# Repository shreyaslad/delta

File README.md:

# Delta

Delta is a minature, custom board that remotely control vehicles, connecting to the Onboard Diagnostics (OBD-II) port and streaming real-time onboard sensor data such as:

- Speed
- Acceleration
- Gyroscopic Tilt
- Throttle & Steering Position
- Gear
- Engine RPM

and integrating external cameras and sensors.

Delta supports WiFi and Bluetooth LE, running a dual-core ESP32-S3R8V based on the 32-bit Xtensa architecture. The current prototype is only 32mm * 37mm with single-sided assembly, packing a ton of components into an incredibly small area. Delta can be powered by a computer through the USB Type-C port or independantly with a 12v car battery.

## Project Structure

```
.
├── docs        : Project documentation
├── firmware    : Delta firmware
├── iot         : AWS IoT infrastructure
├── pcb         : KiCad PCB design files
└── README.md
```

## Hardware

Features:
- USB Type-C connector
- 12v -> 5v @ 3A Buck Converter
- 5v -> 3.3v @ 700mA Low Dropout Regulator
- Dual Core ESP32-S3R8V microcontroller
    - Ultra-low current deep sleep
- 2.4GHz 802.11/b/g/n WiFi
- Bluetooth Low Energy
- CAN bus communication
- Neopixel support

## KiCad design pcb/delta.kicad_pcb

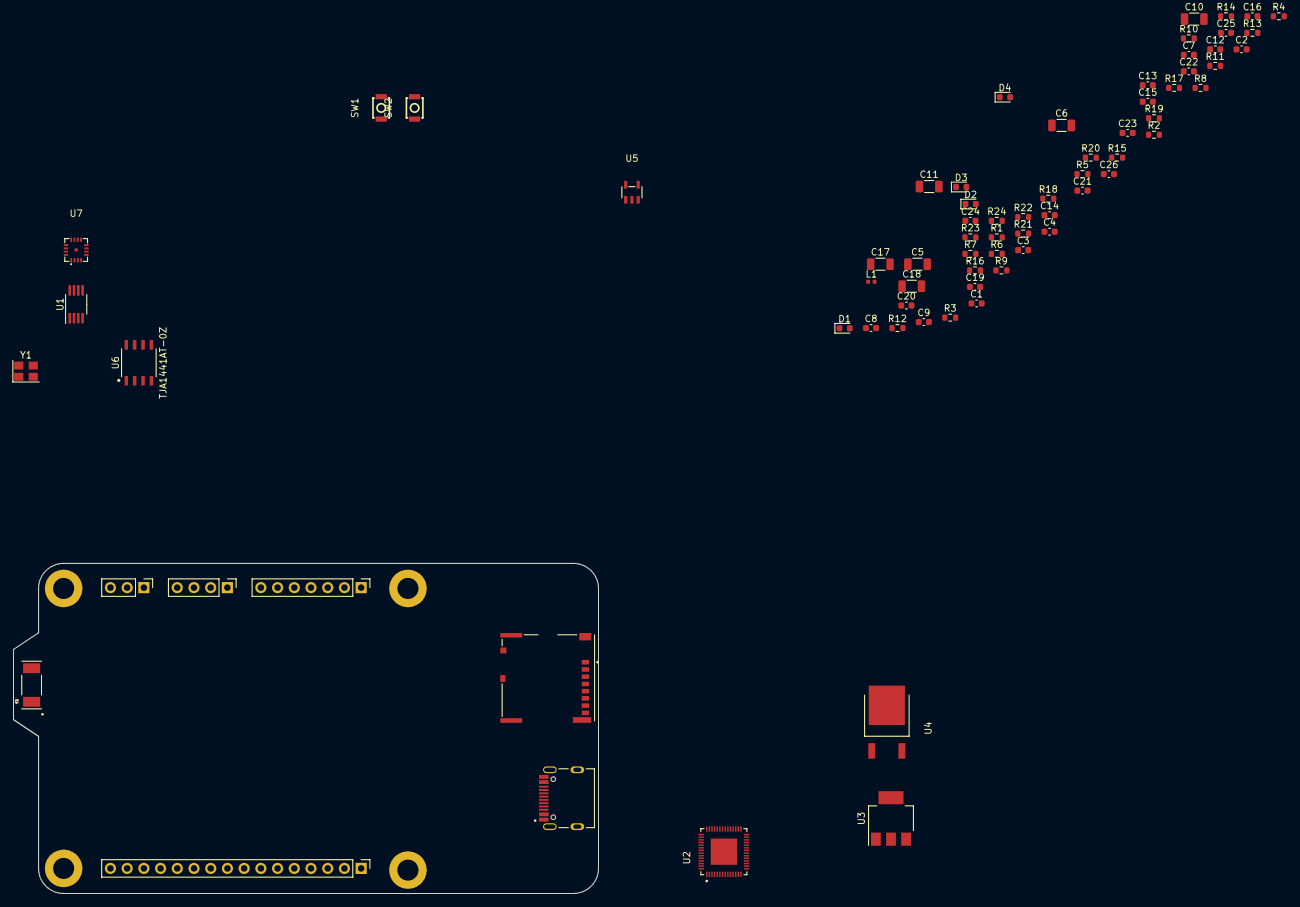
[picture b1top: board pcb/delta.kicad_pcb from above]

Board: 4 copper layers, 88.9 x 50.2 mm, 76 parts (0 on the bottom side), 51 nets, no tracks yet.

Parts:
C1, C3, C4, C13, C14, C15, C16, C19, C22: 1uF; C_0603_1608Metric
C2: 2pF; C_0603_1608Metric
C5, C6, C10, C11, C17, C18: 1uF; C_1206_3216Metric
C7: 10uF; C_0603_1608Metric
C8, C9: 12pF; C_0603_1608Metric
C12, C20, C21, C24, C25, C26: 0.1uF; C_0603_1608Metric
C23: 4.7nF; C_0603_1608Metric
D1: PWR BLUE; LED_0603_1608Metric
D2, D4: D; D_0603_1608Metric
D3: GREEN; LED_0603_1608Metric
E1: NN01-102; XCVR_NN01-102
H1, H2, H3, H4: MountingHole_Pad; MountingHole_3.2mm_M3_ISO7380_Pad
J1: USB_C_Receptacle_USB2.0; HRO_TYPE-C-31-M-12
J2: Conn_01x03; PinHeader_1x03_P2.54mm_Vertical
J3: Conn_01x04; PinHeader_1x04_P2.54mm_Vertical
J4: Conn_01x07; PinHeader_1x07_P2.54mm_Vertical
J5: Conn_01x16; PinHeader_1x16_P2.54mm_Vertical
J6: Micro_SD_Card; MOLEX_503398-1892
L1: 5.1nH; L_0402_1005Metric
R1, R3, R9, R10, R11, R15, R16, R17, R18, R19, R20, R21, R22, R23, R24: 10k; R_0603_1608Metric
R2, R4: 27; R_0603_1608Metric
R5: 270; R_0603_1608Metric
R6, R7: 5.1k; R_0603_1608Metric
R8, R12: 1k; R_0603_1608Metric
R13, R14: 60; R_0603_1608Metric
SW1: RESET; SW-SMD_L3.0-W2.5-P3.40-LS4.0-L
SW2: FLASH; SW-SMD_L3.0-W2.5-P3.40-LS4.0-L
U1: PI4ULS5V202UEX; MSOP-8_3x3mm_P0.65mm
U2: ESP32-S3R8V; QFN40P700X700X90-57N
U3: C401677; SOT-223
U4: CJ78053%; TO-252-2_L6.6-W6.1-P4.58-LS10.1-BR-CW
U5: TPRT9193-18GB; SOT-23-5_L3.0-W1.7-P0.95-LS2.8-BL
U6: TJA1441AT-0Z; TJA1441DT-0Z
U7: QST_QMI8610; LGA-16_L3.3-W3.3-P0.50-BL-EP0.5
Y1: 40 MHz; Crystal_SMD_3225-4Pin_3.2x2.5mm

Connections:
+1V8: C21.1, C25.1, U5.5 (VOUT), U7.8 (VDDd), U7.9 (SA0)
+3V3: C1.1, C7.1, C12.1, C13.1, C14.1, C15.1, C16.1, C17.1, C19.1, C20.1, C24.1, C26.1, J6.4 (VDD), R3.1, R10.1, R15.1, R17.1, R18.1, R19.1, R20.1, R21.1, R22.1, R23.1, R24.1, U1.1 (VCCA), U1.5 (EN), U2.2 (VDD3P3), U2.3 (VDD3P3), U2.20 (VDD3P3_RTC), U2.29 (VDD_SPI), U2.46 (VDD3P3_CPU), U2.55 (VDDA1), U2.56 (VDDA2), U3.3 (VOUT), U5.1 (VIN), U5.3 (EN), U7.2 (VDDa)
/ACCEL_CS: U2.6 (GPIO1), U7.10 (CS)
/ACCEL_INT1: U2.9 (GPIO4), U7.12 (INT1)
/ACCEL_INT2: U2.10 (GPIO5), U7.11 (INT2)
/ACCEL_RST: U2.7 (GPIO2), U7.16 (RST)
/ESP32_Rx: J3.1, U2.50 (U0RXD)
/ESP32_Tx: J3.2, U2.49 (U0TXD)
/ESP32_U0CTS: J3.3, U2.22 (XTAL_32K_N)
/ESP32_U0RTS: J3.4, U2.21 (XTAL_32K_P)
/ESP32_XTAL_N: C9.2, U2.53 (XTAL_N), Y1.1
/ESP32_XTAL_P: C8.2, U2.54 (XTAL_P), Y1.3
/NEOPXL_DIN: U1.2 (A1), U2.14 (GPIO9)
/NEOPXL_DIN_5v: J2.1, R5.2
/OBD_12v: C11.1, J5.7, U4.1 (VIN)
/OBD_CANH: J5.9, R13.1, U6.7 (CANH)
/OBD_CANL: J5.10, R14.2, U6.6 (CANL)
/OBD_Rx: U2.23 (GPIO17), U6.4 (RXD)
/OBD_Tx: U2.24 (GPIO18), U6.1 (TXD)
/SCL: R17.2, U2.11 (GPIO6), U7.14 (SCL)
/SDA: R18.2, U2.12 (GPIO7), U7.13 (SDA)
/SD_CLK: J6.5 (CLK), R21.2, U2.33 (SPICLK)
/SD_CMD: J6.3 (CMD), R22.2, U2.35 (SPID)
/SD_D0: J6.7 (DAT0), R20.2, U2.34 (SPIQ)
/SD_D1: J6.8 (DAT1), R19.2, U2.31 (SPIWP)
/SD_D2: J6.1 (DAT2), R24.2, U2.30 (SPIHD)
/SD_D3: J6.2 (DAT3/CD), R23.2, U2.32 (SPICS0)
/USB_D+: R2.2, U2.26 (GPIO20)
/USB_D-: R4.2, U2.25 (GPIO19)
GND: C1.2, C3.2, C4.2, C5.2, C6.2, C7.2, C8.1, C9.1, C10.2, C11.2, C12.2, C13.2, C14.2, C15.2, C16.2, C17.2, C18.2, C19.2, C20.2, C21.2, C22.2, C23.2, C24.2, C25.2, C26.2, H1.1, H2.1, H3.1, H4.1, J1.A1 (GND), J1.S1 (SHIELD), J2.3, J6.6 (VSS), J6.9 (SHIELD), L1.1, R6.2, R7.2, R8.2, R9.2, R11.2, R12.2, R16.2, SW1.2, SW2.2, U1.4 (GND), U2.57 (GND), U3.2 (GND), U4.2 (GND), U5.2 (GND), U6.2 (GND), U7.3 (GND), U7.15 (GND), Y1.2, Y1.4
unnamed: C2.1, E1.1, L1.2
unnamed: C2.2, U2.1 (LNA_IN)
unnamed: C3.1, R1.1, SW1.1
unnamed: C5.1, C6.1, D1.2 (A), D2.2 (A), J1.A4 (VBUS)
unnamed: C18.1, D4.2 (A), U4.3 (VOUT)
unnamed: C23.1, R13.2, R14.1
unnamed: D1.1 (K), R8.1
unnamed: D3.1 (K), R12.1
unnamed: D3.2 (A), U2.27 (GPIO21)
unnamed: J1.A5 (CC1), R7.1
unnamed: J1.A6 (D+), J1.B6 (D+), R2.1
unnamed: J1.A7 (D-), J1.B7 (D-), R4.1
unnamed: J1.B5 (CC2), R6.1
unnamed: R1.2, R3.2, U2.4 (CHIP_PU)
unnamed: R5.1, U1.7 (B1)
unnamed: R9.1, U2.52 (GPIO46)
unnamed: R10.2, SW2.1, U2.5 (GPIO0)
unnamed: R11.1, U2.8 (GPIO3)
unnamed: R15.2, U6.5 (S_N)
unnamed: R16.1, U6.8 (OFF)
VBUS: C4.1, C10.1, C22.1, D2.1 (K), D4.1 (K), J2.2, U1.8 (VCCB), U3.1 (VIN), U6.3 (VCC)

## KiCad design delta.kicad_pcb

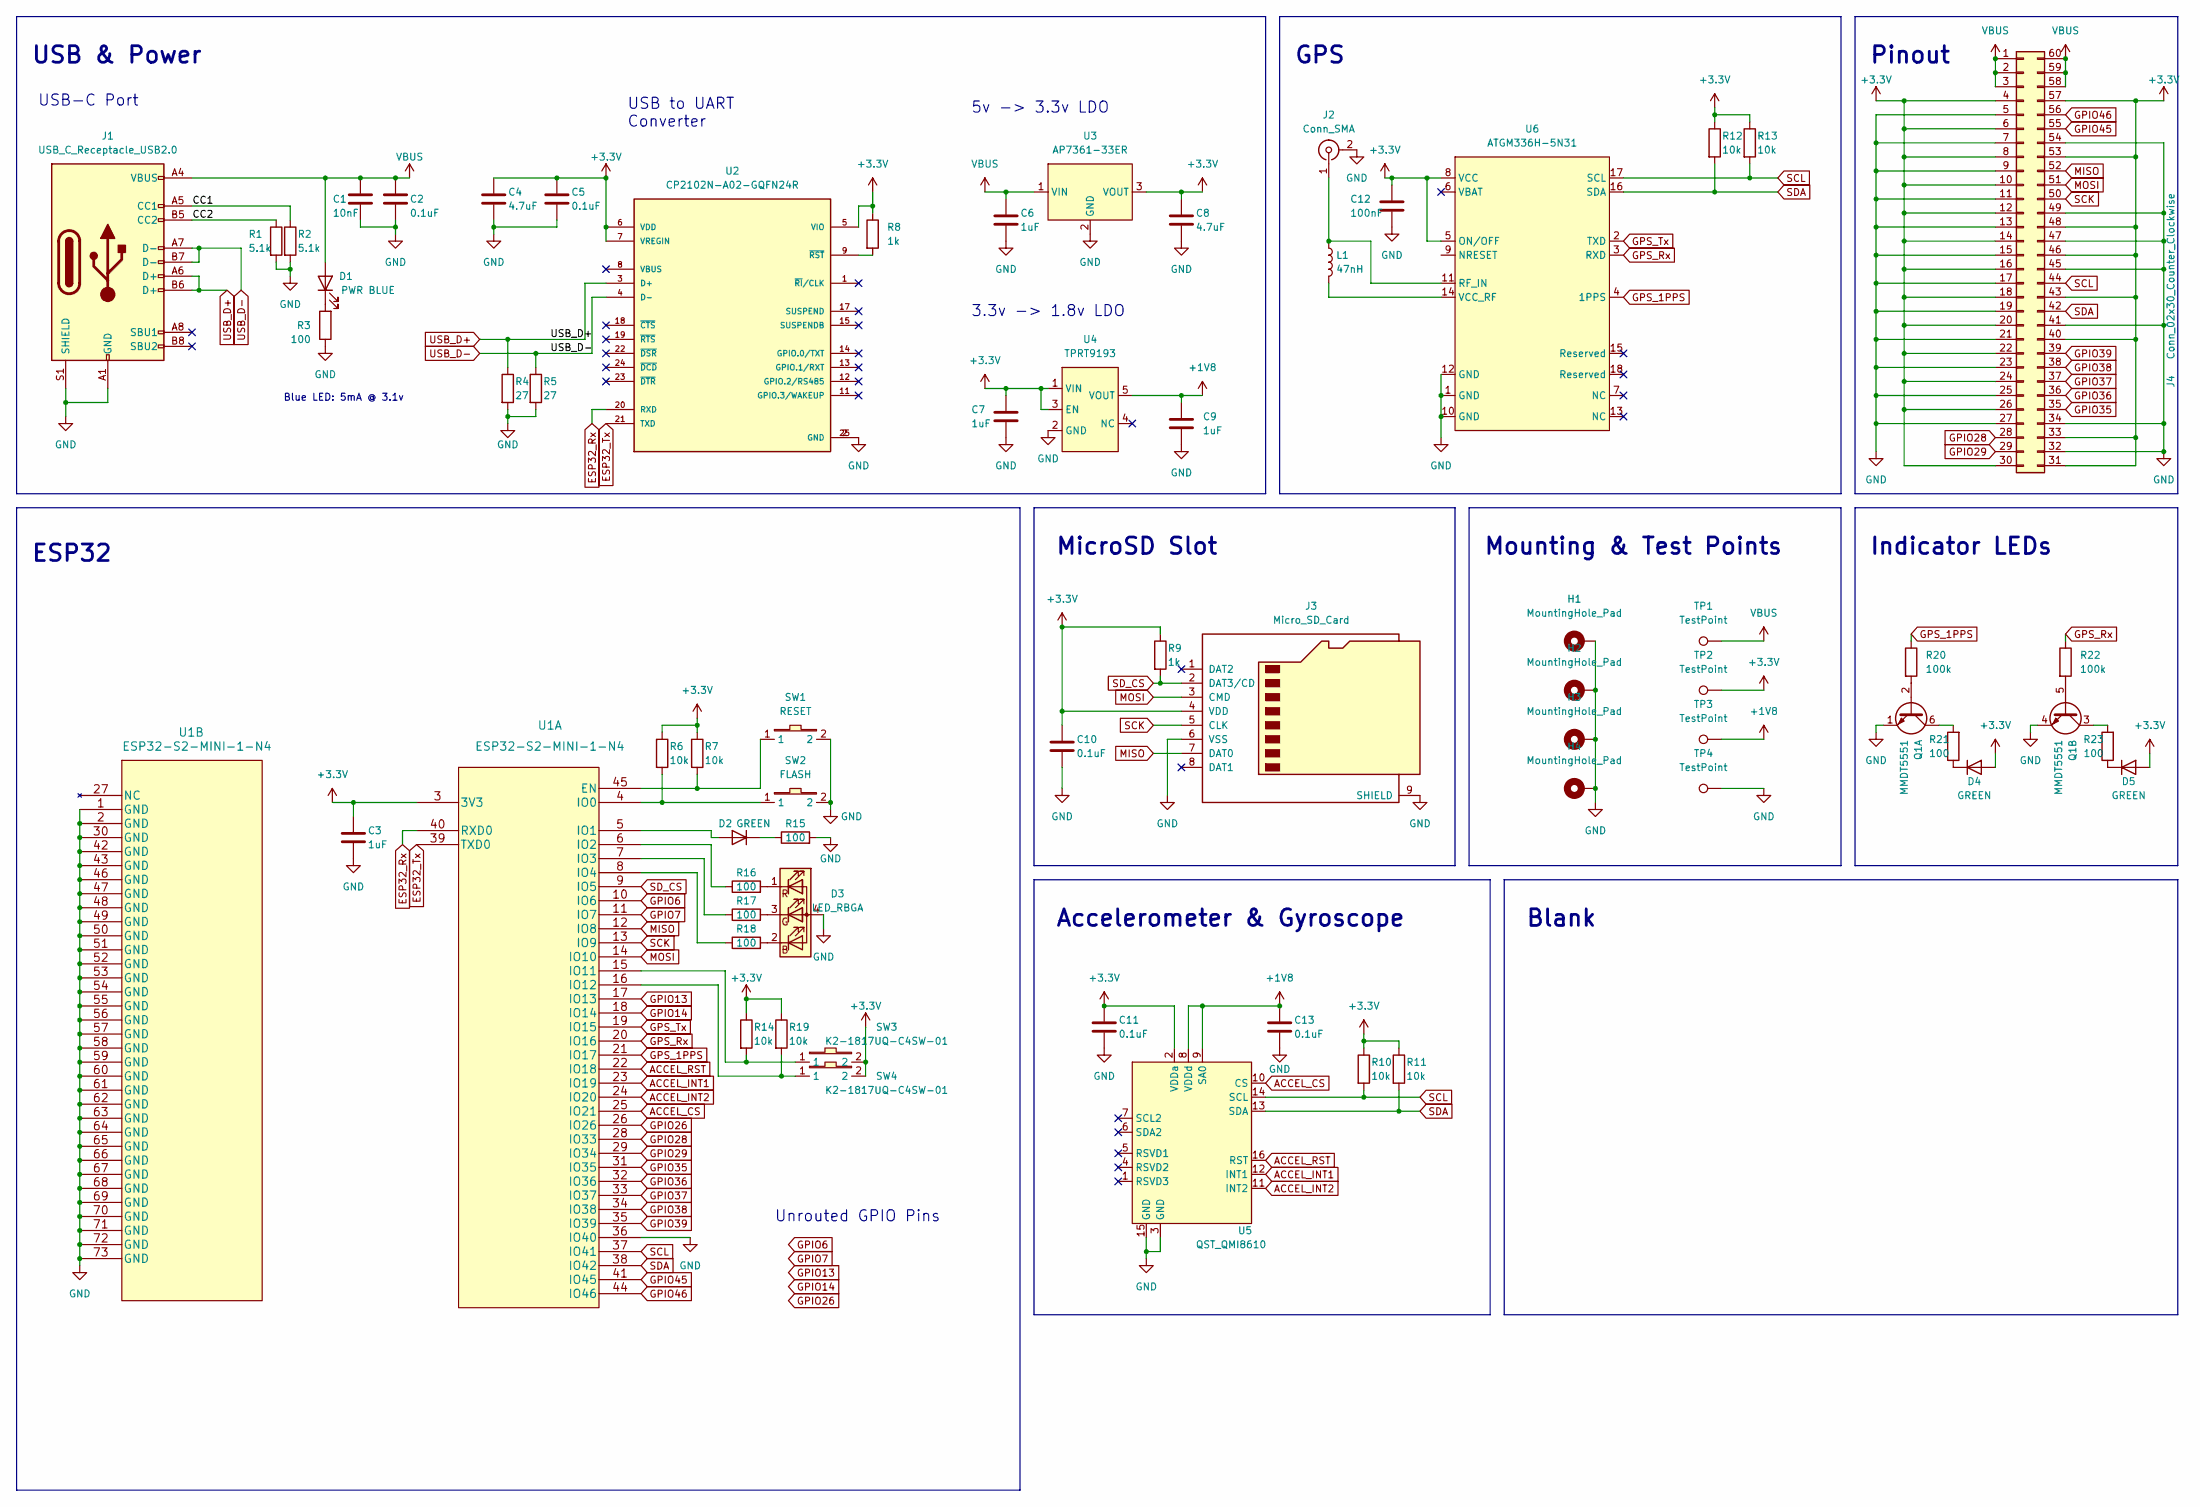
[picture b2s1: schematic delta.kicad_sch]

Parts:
C1: 10nF; C_1206_3216Metric
C2: 0.1uF; C_1206_3216Metric
C3, C6: 1uF; C_1206_3216Metric
C4: 4.7uF; C_0603_1608Metric
C5, C10, C11, C13: 0.1uF; C_0603_1608Metric
C7, C9: 1uF; C_0603_1608Metric
C8: 4.7uF; C_1206_3216Metric
C12: 100nF; C_0603_1608Metric
D1: PWR BLUE; LED_0805_2012Metric
D2: GREEN; LED_0805_2012Metric
D3: LED_RBGA; LED_RGB_1210
D4, D5: GREEN; LED_0603_1608Metric
H1, H2, H3, H4: MountingHole_Pad; MountingHole_3.2mm_M3_ISO7380_Pad
J1: USB_C_Receptacle_USB2.0; HRO_TYPE-C-31-M-12
J2: Conn_SMA; ANT-SMD_1909763-1
J3: Micro_SD_Card; MOLEX_503398-1892
J4: Conn_02x30_Counter_Clockwise; PinHeader_2x30_P2.00mm_Vertical
L1: 47nH; L_0603_1608Metric
Q1: MMDT5551; SOT-363_SC-70-6
R1, R2: 5.1k; R_0603_1608Metric
R3, R15, R16, R17, R18, R21, R23: 100; R_0603_1608Metric
R4, R5: 27; R_0603_1608Metric
R6, R7, R10, R11, R12, R13, R14, R19: 10k; R_0603_1608Metric
R8, R9: 1k; R_0603_1608Metric
R20, R22: 100k; R_0603_1608Metric
SW1: RESET; KEY-SMD_2P-L6.0-W6.0-P6.00; LCSC Part C128939
SW2: FLASH; KEY-SMD_2P-L6.0-W6.0-P6.00; LCSC Part C128939
SW3, SW4: K2-1817UQ-C4SW-01; KEY-SMD_2P-L6.0-W6.0-P6.00; LCSC Part C128939
TP1, TP2, TP3, TP4: TestPoint; TestPoint_Pad_D3.0mm
U1: ESP32-S2-MINI-1-N4
U2: CP2102N-A02-GQFN24R; QFN50P400X400X80-25N; PARTREV 1.3
U3: AP7361-33ER; SOT-223
U4: TPRT9193; SOT-23-5_L3.0-W1.7-P0.95-LS2.8-BL
U5: QST_QMI8610; LGA-16_L3.3-W3.3-P0.50-BL-EP0.5
U6: ATGM336H-5N31; GPSM-SMD_ATGM336H-TR; LCSC Part C90770

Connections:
+1V8: C9.1, C13.1, TP3.1, U4.5 (VOUT), U5.8 (VDDd), U5.9 (SA0)
+3V3: C3.1, C4.1, C5.1, C7.1, C8.1, C10.1, C11.1, C12.1, D4.2 (A), D5.2 (A), J3.4 (VDD), J4.4, J4.6, J4.8, J4.10, J4.12, J4.14, J4.16, J4.18, J4.20, J4.22, J4.24, J4.26, J4.30, J4.31, J4.33, J4.40, J4.43, J4.46, J4.48, J4.53, J4.57, R6.1, R7.1, R8.1, R9.1, R10.1, R11.1, R12.1, R13.1, R14.1, R19.1, SW3.2, SW4.2, TP2.1, U1.3 (3V3), U2.5 (VIO), U2.6 (VDD), U2.7 (VREGIN), U3.3 (VOUT), U4.1 (VIN), U4.3 (EN), U5.2 (VDDa), U6.5 (ON/OFF), U6.8 (VCC)
/CC1: J1.A5 (CC1), R2.1
/CC2: J1.B5 (CC2), R1.1
ACCEL_CS: U1.25 (IO21), U5.10 (CS)
ACCEL_INT1: U1.23 (IO19), U5.12 (INT1)
ACCEL_INT2: U1.24 (IO20), U5.11 (INT2)
ACCEL_RST: U1.22 (IO18), U5.16 (RST)
ESP32_Rx: U1.40 (RXD0), U2.20 (RXD)
ESP32_Tx: U1.39 (TXD0), U2.21 (TXD)
GND: C1.2, C2.2, C3.2, C4.2, C5.2, C6.2, C7.2, C8.2, C9.2, C10.2, C11.2, C12.2, C13.2, D3.4 (A), H1.1, H2.1, H3.1, H4.1, J1.A1 (GND), J1.A12 (GND), J1.B1 (GND), J1.B12 (GND), J1.S1 (SHIELD), J2.2 (Ext), J3.6 (VSS), J3.9 (SHIELD), J4.5, J4.7, J4.9, J4.11, J4.13, J4.15, J4.17, J4.19, J4.21, J4.23, J4.25, J4.27, J4.32, J4.34, J4.41, J4.45, J4.47, J4.49, J4.54, Q1.1 (E1), Q1.4 (E2), R1.2, R2.2, R3.1, R4.2, R5.2, R15.2, SW1.2, SW2.2, TP4.1, U1.1 (GND), U1.2 (GND), U1.30 (GND), U1.36 (IO40), U1.42 (GND), U1.43 (GND), U1.46 (GND), U1.47 (GND), U1.48 (GND), U1.49 (GND), U1.50 (GND), U1.51 (GND), U1.52 (GND), U1.53 (GND), U1.54 (GND), U1.55 (GND), U1.56 (GND), U1.57 (GND), U1.58 (GND), U1.59 (GND), U1.60 (GND), U1.61 (GND), U1.62 (GND), U1.63 (GND), U1.64 (GND), U1.65 (GND), U1.66 (GND), U1.67 (GND), U1.68 (GND), U1.69 (GND), U1.70 (GND), U1.71 (GND), U1.72 (GND), U1.73 (GND), U2.2 (GND), U2.25 (GND), U3.2 (GND), U4.2 (GND), U5.3 (GND), U5.15 (GND), U6.1 (GND), U6.10 (GND), U6.12 (GND)
GPIO6: U1.10 (IO6)
GPIO7: U1.11 (IO7)
GPIO13: U1.17 (IO13)
GPIO14: U1.18 (IO14)
GPIO26: U1.26 (IO26)
GPIO28: J4.28, U1.28 (IO33)
GPIO29: J4.29, U1.29 (IO34)
GPIO35: J4.35, U1.31 (IO35)
GPIO36: J4.36, U1.32 (IO36)
GPIO37: J4.37, U1.33 (IO37)
GPIO38: J4.38, U1.34 (IO38)
GPIO39: J4.39, U1.35 (IO39)
GPIO45: J4.55, U1.41 (IO45)
GPIO46: J4.56, U1.44 (IO46)
GPS_1PPS: R20.1, U1.21 (IO17), U6.4 (1PPS)
GPS_Rx: R22.1, U1.20 (IO16), U6.3 (RXD)
GPS_Tx: U1.19 (IO15), U6.2 (TXD)
MISO: J3.7 (DAT0), J4.52, U1.12 (IO8)
MOSI: J3.3 (CMD), J4.51, U1.14 (IO10)
unnamed: D1.1 (K), R3.2
unnamed: D2.1 (K), R15.1
unnamed: D2.2 (A), U1.5 (IO1)
unnamed: D3.1 (RK), R16.2
unnamed: D3.2 (BK), R18.2
unnamed: D3.3 (GK), R17.2
unnamed: D4.1 (K), R21.1
unnamed: D5.1 (K), R23.1
unnamed: J2.1 (In), L1.1, U6.11 (RF_IN)
unnamed: L1.2, U6.14 (VCC_RF)
unnamed: Q1.2 (B1), R20.2
unnamed: Q1.3 (C2), R23.2
unnamed: Q1.5 (B2), R22.2
unnamed: Q1.6 (C1), R21.2
unnamed: R6.2, SW2.1, U1.4 (IO0)
unnamed: R7.2, SW1.1, U1.45 (EN)
unnamed: R8.2, U2.9 (~RST)
unnamed: R14.2, SW3.1, U1.15 (IO11)
unnamed: R16.1, U1.6 (IO2)
unnamed: R17.1, U1.7 (IO3)
unnamed: R18.1, U1.8 (IO4)
unnamed: R19.2, SW4.1, U1.16 (IO12)
SCK: J3.5 (CLK), J4.50, U1.13 (IO9)
SCL: J4.44, R10.2, R13.2, U1.37 (IO41), U5.14 (SCL), U6.17 (SCL)
SDA: J4.42, R11.2, R12.2, U1.38 (IO42), U5.13 (SDA), U6.16 (SDA)
SD_CS: J3.2 (DAT3/CD), R9.2, U1.9 (IO5)
USB_D+: J1.A6 (D+), J1.B6 (D+), R4.1, U2.3 (D+)
USB_D-: J1.A7 (D-), J1.B7 (D-), R5.1, U2.4 (D-)
VBUS: C1.1, C2.1, C6.1, D1.2 (A), J1.A4 (VBUS), J1.A9 (VBUS), J1.B4 (VBUS), J1.B9 (VBUS), J4.1, J4.2, J4.3, J4.58, J4.59, J4.60, TP1.1, U3.1 (VIN)

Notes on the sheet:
MicroSD Slot
Accelerometer & Gyroscope
Blue LED: 5mA @ 3.1v
Pinout
USB to UART Converter
Mounting & Test Points
USB-C Port
3.3v -> 1.8v LDO
5v -> 3.3v LDO
Unrouted GPIO Pins
GPS
Indicator LEDs
Blank
ESP32
USB & Power

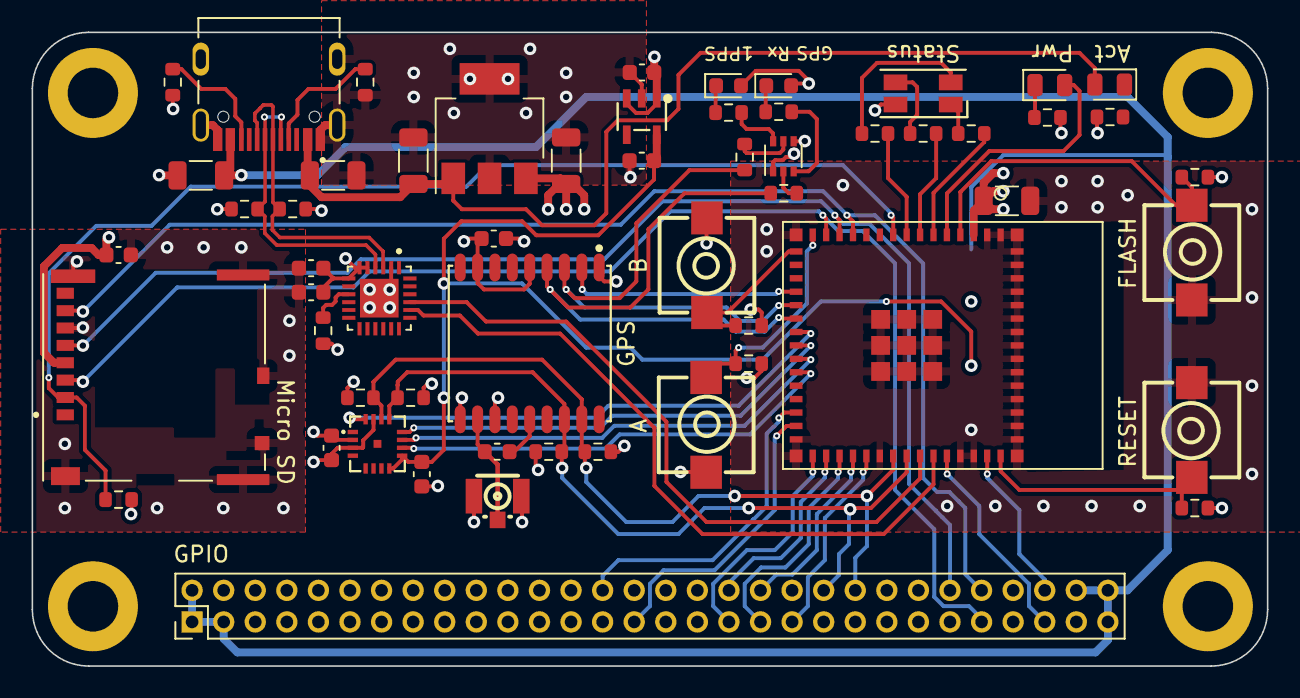
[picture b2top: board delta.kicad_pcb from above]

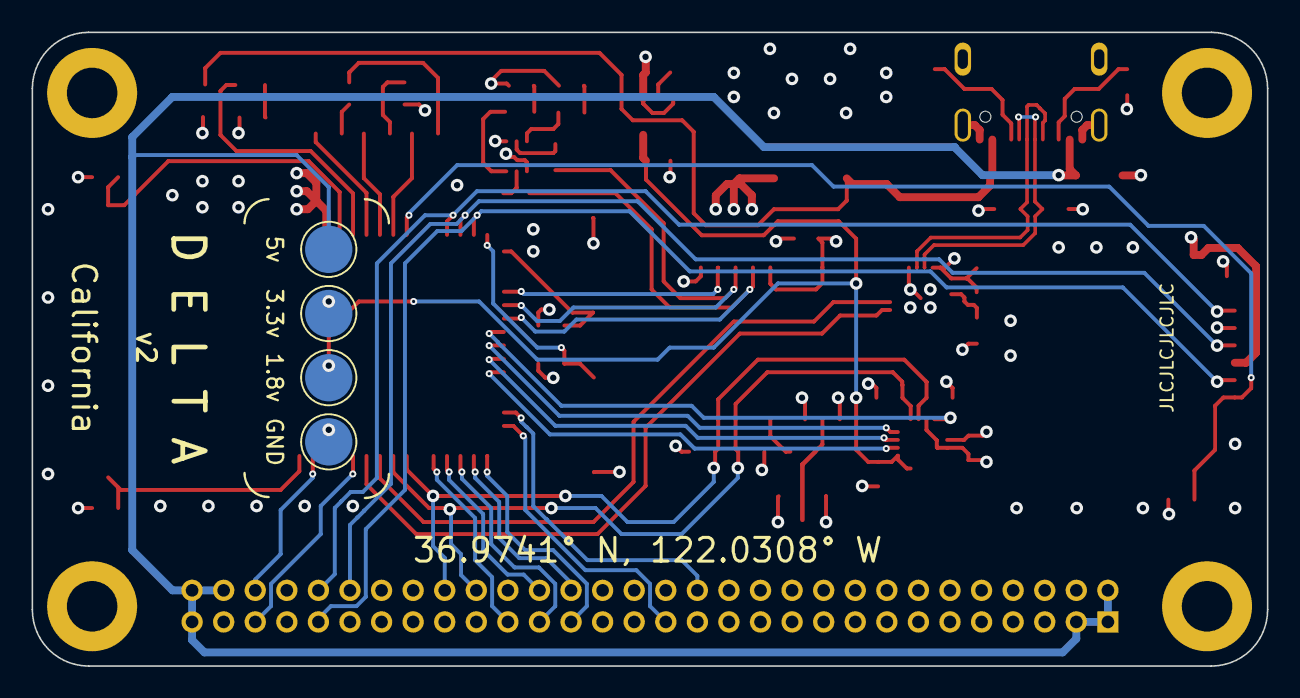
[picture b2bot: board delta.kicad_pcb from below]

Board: 4 copper layers, 78.2 x 40.1 mm, 65 parts (4 on the bottom side), 54 nets.

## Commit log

2022-05-16 Remove external LDO, use converter's inbuilt one
2022-05-16 Rewire CBUS1 & CBUS2 to add indicator LEDs
2022-05-16 FT231XS-R USB to UART footprints filled
2022-06-11 Initial (now defunct) accel and gyro
2022-06-14 Most routing complete, except temp sensor. Last 2 layer version
2022-06-14 4 layers, removed routing
2022-06-23 final v1 routing
2022-07-09 v2 initial design, rework likely
2022-07-24 Initial v2 routing
2022-07-26 Added I2C pullups and indicator LEDs
2022-07-26 final fixes
2022-07-26 update new led resistor values
2022-07-26 update silkscreen around test points
2022-10-25 v4 prototype + refactor
2022-10-26 fix: Update readme, add boilerplate code
2022-10-26 fix: remove unnecessary files
2024-05-02 feat: remove everything unnecessary

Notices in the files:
delta.kicad_pcb:
MIT License
parts and their libraries:
Copyright 2021 Accelerated Designs. All rights reserved.
